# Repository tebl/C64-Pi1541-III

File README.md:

# C64 Pi1541-III
Well... if you're here, then that new and shiny SD2IEC for your Commodore 64 wasn't cycle-exact enough for you? Sure, there are great FPGA-based solutions available that can be purchased at a premium pricepoint. For the rest of us who are either on a tight budget - or - simply want something that they can build at home, then the excellent Pi1541-software written by Steve White may very well be the solution you've been looking for. With a Raspberry Pi 3 at its core, it is able to provide cycle-exact disk drive emulation with many improvements over the drive you had in your youth!

A Pi1541 can be constructed in many ways, but even though you can easily build one without the help of a PCB such as the ones provided by this project - I've found it a lot easier to make them work when you have a PCB available. I've released the design files for a more traditional Raspberry Pi-hat if you would rather build one of those, these can be found in my old repository at [C64-Pi1541-Module](https://github.com/tebl/C64-Pi1541-Module). A slightly different take on the device can also be found at [C64-Pi1541-II](https://github.com/tebl/C64-Pi1541-II) as it was made to resemble a slightly smaller stack of floppy disks.

With this third version I've instead attempted to make one that's more akin to a modern device, incorporating a 1.3" OLED on the front as being controlled via the use of a rotary encoder. While the design aesthetic makes it slightly harder to build than your standard Pi1541, I believe that it more than makes up for it.

- [1> Modules](#1-modules)
- [2> Documentation](#2-documentation)
  - [2.1> Resources](#21-resources)
- [3> Acknowledgements](#3-acknowledgements)

## 1> Modules
A complete Pi1541 requires no less than five PCBs in order to be built as pictured, for a somewhat simpler build you may skip the bottom faceplate though that also serves a purpose and it wouldn't entirely be complete without it. See below for a side view of how the device is put together, there is a top and bottom faceplate as well as another faceplate on the front. The PCB at the center will in the documentation be referred to as the *Pi1541-III Module* while the smaller one towards the front will be referred to as the *panel*.

In order to keep things in an order that's mostly organized, I've had to separate out information such as the *BOM* that goes into the build for the modules they belong to - hopefully making things easier if I ever start doing alternate versions with other components. See further below for [documentation](#2-documentation) on how to assemble one, set it up as well as anything else that you might need to know.

| Module                 | Required    | Description                        | Documentation                      | Order      |
| ---------------------- | ----------- | ---------------------------------- | ---------------------------------- | ---------- |
| [C64 Pi1541-III Module](https://github.com/tebl/C64-Pi1541-III/tree/main/C64%20Pi1541-III%20Module) | Yes | Main module |  [BOM](https://github.com/tebl/C64-Pi1541-III/tree/main/C64%20Pi1541-III%20Module/README.md#3-bom) | [PCBWay](https://www.pcbway.com/project/shareproject/C64_Pi1541_III_Module_629bebca.html)
| [C64 Pi1541-III Module Panel](https://github.com/tebl/C64-Pi1541-III/tree/main/C64%20Pi1541-III%20Module%20Panel) | Yes | Adds a vertical surface for mounting switches and rotary encoder. |  [BOM](https://github.com/tebl/C64-Pi1541-III/tree/main/C64%20Pi1541-III%20Module%20Panel/README.md#3-bom) | [PCBWay](https://www.pcbway.com/project/shareproject/C64_Pi1541_III_Panel_39049bfb.html)
| [C64 Pi1541-III Faceplate (FB1)](https://github.com/tebl/C64-Pi1541-III/tree/main/faceplates/C64%20Pi1541-III%20Module%20FB1) | Yes | Top faceplate, provides mechanical support for front panel. | | [PCBWay](https://www.pcbway.com/project/shareproject/C64_Pi1541_III_Faceplate_FB1_d125443d.html)
| [C64 Pi1541-III Faceplate (FB2)](https://github.com/tebl/C64-Pi1541-III/tree/main/faceplates/C64%20Pi1541-III%20Module%20FB2) | Recommended | Bottom faceplate, adds a layer of security so that you don't accidentally short out the device on something placed under it. | | [PCBWay](https://www.pcbway.com/project/shareproject/C64_Pi1541_III_Faceplate_FB2_912f9cbb.html)
| [C64 Pi1541-III Faceplate (FP1)](https://github.com/tebl/C64-Pi1541-III/tree/main/faceplates/C64%20Pi1541-III%20Module%20FP1) | Recommended | Front faceplate, this is mainly here to make things look nice. | | [PCBWay](https://www.pcbway.com/project/shareproject/C64_Pi1541_III_Faceplate_FP1_228805ce.html)

# 2> Documentation
There are many things that need to be said in order to successfully put a working Pi1541 together, and while the information may seem pedantic and at that times simplified for veterans at building electronical devices - I'm just an amateur and so I try to include everything that would have been needed when I first started building things such as this.

If you've just come across this page and have been wondering exactly what components you need to order in order to build the Pi1541, then I suggest that you start on the [modules](#1-modules)-section - each of modules listed are PCBs that you will most likely want. In the same list there is a link to the BOM belonging to that specific module, you need to order the components for each of them.

This repository does not include Gerber-files, you either need to generate those from the KiCAD source files found in this repository - the easiest way to order them via [PCBWay](https://www.pcbway.com/project/shareproject/?tag=Pi1541-III). Note that for the faceplates specifically, you may want to pay a little bit extra to avoid having the order number printed on it - or specifically tell them to put it on the back.

For everything else, I can only hope that one of the following documents will provide you with the answers that you need:
- [Assembling one](https://github.com/tebl/C64-Pi1541-III/blob/main/documentation/assembling_one.md)
- [Setting it up](https://github.com/tebl/C64-Pi1541-III/blob/main/documentation/setting_it_up.md)
- [Troubleshooting](https://github.com/tebl/C64-Pi1541-III/blob/main/documentation/troubleshooting.md)

## 2.1> Resources
- [Pi1541 Homepage](https://cbm-pi1541.firebaseapp.com/)
- [fat32format](http://ridgecrop.co.uk/index.htm?guiformat.htm)
- [Shared PCBWay projects for Pi1541-III](https://www.pcbway.com/project/shareproject/?tag=Pi1541-III)

# 3> Acknowledgements
Everything comes from something, in particular when it comes to most of my electronics projects. I mainly build things I would like to own, often doing a respin to fit my own particular style and preferences with most of the hardest parts of the designs already provided by people more knowledgable than I.

The Pi1541-III would not exist if it were not for the work of Steve White, creator of the [Pi1541](https://cbm-pi1541.firebaseapp.com/)-software that makes this jumble of PCBs come alive!

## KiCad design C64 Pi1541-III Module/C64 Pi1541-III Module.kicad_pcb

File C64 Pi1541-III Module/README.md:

# Pi1541-III Module
This is the main PCB and will hold most of the active components in the device, but note that it is designed to be used with [Pi1541-III Module Panel](https://github.com/tebl/C64-Pi1541-III/tree/main/C64%20Pi1541-III%20Module%20Panel) and has one listed in the [BOM](#3-bom). Note that the mentioned panel also has its own separate [BOM](https://github.com/tebl/C64-Pi1541-III/tree/main/C64%20Pi1541-III%20Module%20Panel/README.md#3-bom), so keep that in mind while ordering components.

- [1> Build instructions](#1-build-instructions)
- [2> Schematic](#2-schematic)
- [3> BOM](#3-bom)

# 1> Build instructions
Assembling this module is covered as part of the overall documentation, as linked below. Note that *BOM* is supplied per module, the one belonging to this module in particular is included as part of this document (click [here](#3-bom) to go there).

- [Assembling one](https://github.com/tebl/C64-Pi1541-III/blob/main/documentation/assembling_one.md)

# 2> Schematic
The supplied KiCad files should be sufficient as both a schematic and as a  starting point for ordering PCBs (basically you could just zip the contents of the export folder and upload that on a fabrication site), the schematic is also available in [PDF-format](https://github.com/tebl/C64-Pi1541-III/tree/main/documentation/schematic) and this is what you'll need to print and work your way through this things don't work as expected after assembly.

# 3> BOM
Most parts should be easy to get a hold of from your favourite local electronic component shop, but given that I don't have access to such shops where I live so everything was based on whatever I could get cheapest from eBay/AliExpress (free shipping, but plan on waiting 3-4 weeks for delivery). Components in parenthesis can be considered optional for features beyond the more basic functionality, but where's the fun in that? You deserve the complete package.

| Reference             | Item                                                              | Count | Order  |
| --------------------- | ----------------------------------------------------------------- | ----- | ------ |
| Module PCB            | PCB specific to this project                                      |     1 | [See modules](https://github.com/tebl/C64-Pi1541-III/blob/main/README.md#1-modules)
| Faceplate (FB1) PCB   | Top faceplate                                                     |     1 | [See modules](https://github.com/tebl/C64-Pi1541-III/blob/main/README.md#1-modules)
| Faceplate (FB2) PCB   | Bottom faceplate                                                  |    (1)| [See modules](https://github.com/tebl/C64-Pi1541-III/blob/main/README.md#1-modules)
| A1                    | 2x20 pin female header                                            |     1 |
|                       | Raspberry Pi version 3B,3B+ or 3A+                                |     1 |
| A2 *1                 | 4ch I2C level converter module                                    |     1 |
| BZ1                   | Passive buzzer (pin spacing from 3.81 to 7mm will work)           |   (1) |
| C1                    | 100nF ceramic capacitor (5mm)                                     |     1 |
| C6                    | 470uF electrolytic capacitor (8mm x 3.5mm)                        |     1 |
| J1                    | 2.1mm x 5.5mm barrel plug                                         |     1 |
| J2,J3                 | Female S-terminal 6-pin DIN PCB                                   |  1 (1)|
| J8                    | [Pi1541-III Module Panel](https://github.com/tebl/C64-Pi1541-III/tree/main/C64%20Pi1541-III%20Module%20Panel) (completed unit) | 1 |
| R1,R2                 | 1k Ohm resistor                                                   |     2 |
| R3,R4                 | 10k Ohm resistor                                                  |     2 |
| R6,R7 *2              | 470 Ohm resistor                                                  |     2 |
| U1 *3                 | 7406 (DIP-14)                                                     |     1 |
| Mounting *4           | Nylon M3 hex standoffs 6mm (M-F)                                  |     4 |
| Mounting *4           | Nylon M3 hex standoffs 8mm (M-F)                                  |     2 |
| Mounting *5           | Nylon M3 hex standoffs 12mm (M-F)                                 |    (4)|
| Mounting *4           | Nylon M3 hex standoffs 20mm (M-F)                                 |     4 |
| Mounting *4           | Nylon M3x6mm nylon screws                                         |     6 |
| Mounting *4           | Nylon M3x6mm nylon nuts                                           |     12 |

1) There are multiple configurations of these being sold, this is usually sold with a blue PCB. When in doubt, compare the sale listing with the one shown in this [image](https://raw.githubusercontent.com/tebl/C64-Pi1541-III/main/gallery/build_006B.jpg).
2) This is the resistor for the LEDs mounted on [Pi1541-III Module Panel](https://github.com/tebl/C64-Pi1541-III/tree/main/C64%20Pi1541-III%20Module%20Panel), the value need to be sized according to the type of LED being used. This value is a somewhat safe choice cheaper coloured LEDs, for anything blue or especially marked as being *bright* - then you need to calculate a proper value for these.
3) There are unfortunately counterfeit 7406-chips being circulated, the ones I've had the most success with has been marked 7406PC though a handful of SN7406 have also been found working. See [troubleshooting](https://github.com/tebl/C64-Pi1541-III/blob/main/documentation/troubleshooting.md) for more information.
4) These are used in various places of the project, these are available in the form of kits usually advertised *M3 nylon standoff kit* which should contain most of what you'd need though you should check that they include them in sufficient quantity.
5) These are only needed when *NOT* installing bottom faceplate ([Pi1541-III Faceplate (FB2)](https://github.com/tebl/C64-Pi1541-III/tree/main/faceplates/C64%20Pi1541-III%20Module%20FB2))

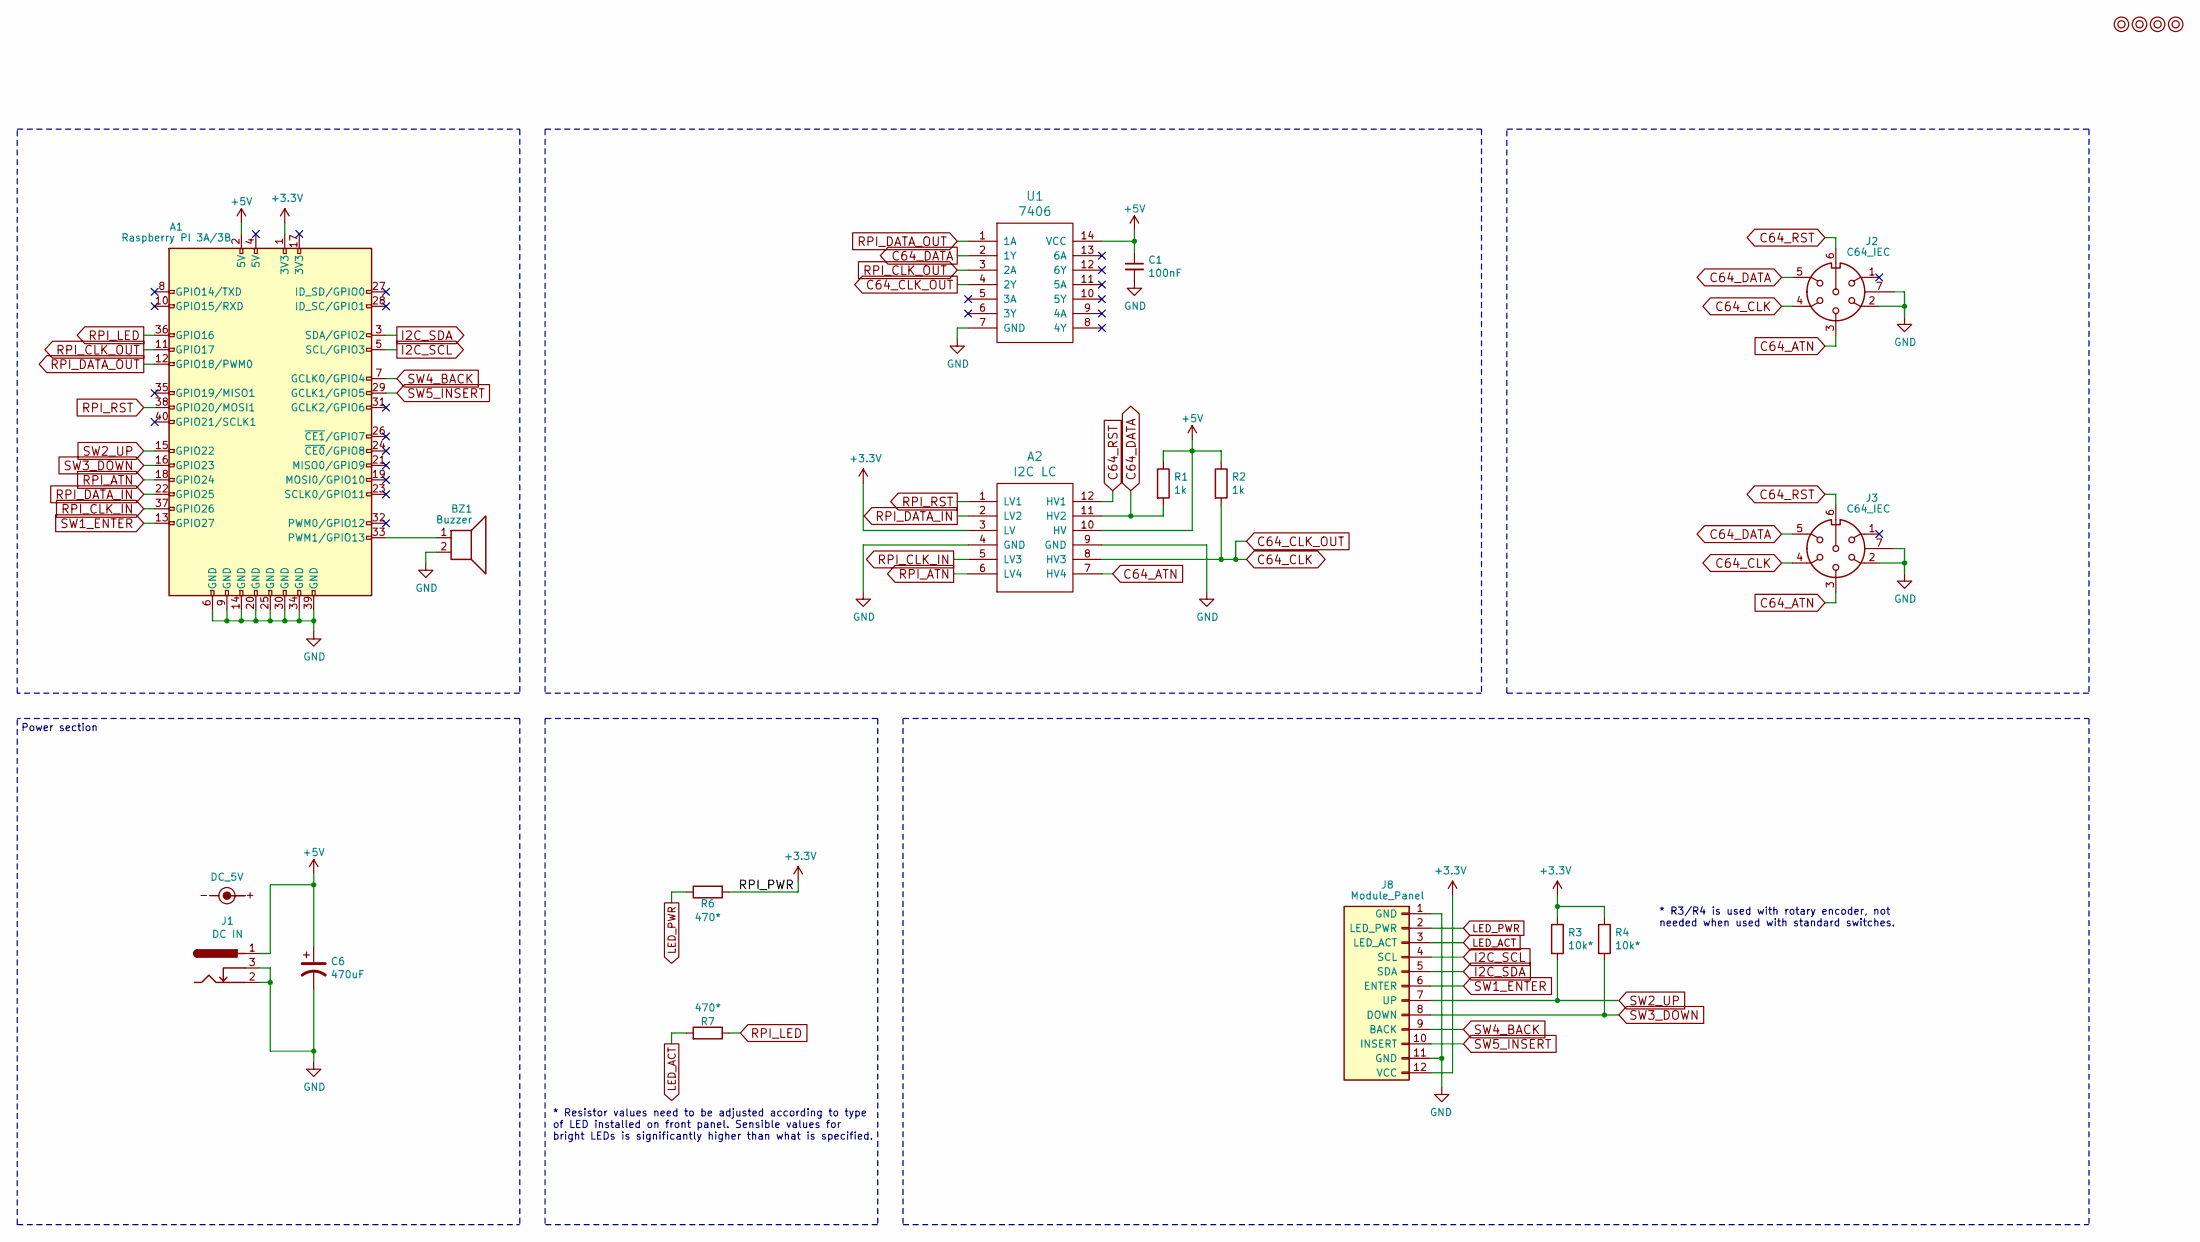
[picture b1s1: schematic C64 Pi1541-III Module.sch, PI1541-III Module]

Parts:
A1: Raspberry PI 3A/3B; Raspberry_Pi_3B_Socketed_THT_FaceDown_MountingHoles
A2: I2C LC; 4CH_I2C_Level_Converter
BZ1: Buzzer; Buzzer_12x9.5RM7.6
C1: 100nF; C_Disc_D4.7mm_W2.5mm_P5.00mm
C6: 470uF; CP_Radial_D8.0mm_P3.50mm
J1: DC IN; BARREL_JACK
J2, J3: C64_IEC; DIN6_IEC
J8: Module_Panel
M1, M2, M3, M4: Mounting; M3
R1, R2: 1k; R_Axial_DIN0207_L6.3mm_D2.5mm_P10.16mm_Horizontal
R3, R4: 10k*; R_Axial_DIN0207_L6.3mm_D2.5mm_P10.16mm_Horizontal
R6, R7: 470*; R_Axial_DIN0207_L6.3mm_D2.5mm_P10.16mm_Horizontal
SYM1: DC_5V; PWR_Specification
U1: 7406; DIP-14_W7.62mm_Socket_LongPads

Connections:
+3V3: A1.1 (3V3), A2.3 (LV), J8.12 (VCC), R3.1, R4.1, R6.2
+5V: A1.2 (5V), A2.10 (HV), C1.1, C6.1, J1.1, R1.1, R2.1, U1.14 (VCC)
C64_ATN: A2.7 (HV4), J2.3, J3.3
C64_CLK: A2.8 (HV3), J2.4, J3.4, R2.2, U1.4 (2Y)
C64_DATA: A2.11 (HV2), J2.5, J3.5, R1.2, U1.2 (1Y)
C64_RST: A2.12 (HV1), J2.6, J3.6
GND: A1.6 (GND), A1.9 (GND), A1.14 (GND), A1.20 (GND), A1.25 (GND), A1.30 (GND), A1.34 (GND), A1.39 (GND), A2.4 (GND), A2.9 (GND), BZ1.2, C1.2, C6.2, J1.2, J1.3, J2.2, J2.7, J3.2, J3.7, J8.1 (GND), J8.11 (GND), U1.7 (GND)
I2C_SCL: A1.5 (SCL/GPIO3), J8.4 (SCL)
I2C_SDA: A1.3 (SDA/GPIO2), J8.5 (SDA)
LED_ACT: J8.3 (LED_ACT), R7.2
LED_PWR: J8.2 (LED_PWR), R6.1
unnamed: A1.33 (PWM1/GPIO13), BZ1.1
RPI_ATN: A1.18 (GPIO24), A2.6 (LV4)
RPI_CLK_IN: A1.37 (GPIO26), A2.5 (LV3)
RPI_CLK_OUT: A1.11 (GPIO17), U1.3 (2A)
RPI_DATA_IN: A1.22 (GPIO25), A2.2 (LV2)
RPI_DATA_OUT: A1.12 (GPIO18/PWM0), U1.1 (1A)
RPI_LED: A1.36 (GPIO16), R7.1
RPI_RST: A1.38 (GPIO20/MOSI1), A2.1 (LV1)
SW1_ENTER: A1.13 (GPIO27), J8.6 (ENTER)
SW2_UP: A1.15 (GPIO22), J8.7 (UP), R3.2
SW3_DOWN: A1.16 (GPIO23), J8.8 (DOWN), R4.2
SW4_BACK: A1.7 (GCLK0/GPIO4), J8.9 (BACK)
SW5_INSERT: A1.29 (GCLK1/GPIO5), J8.10 (INSERT)

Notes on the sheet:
Power section
* R3/R4 is used with rotary encoder, not needed when used with standard switches.
* Resistor values need to be adjusted according to type of LED installed on front panel. Sensible values for bright LEDs is significantly higher than what is specified.

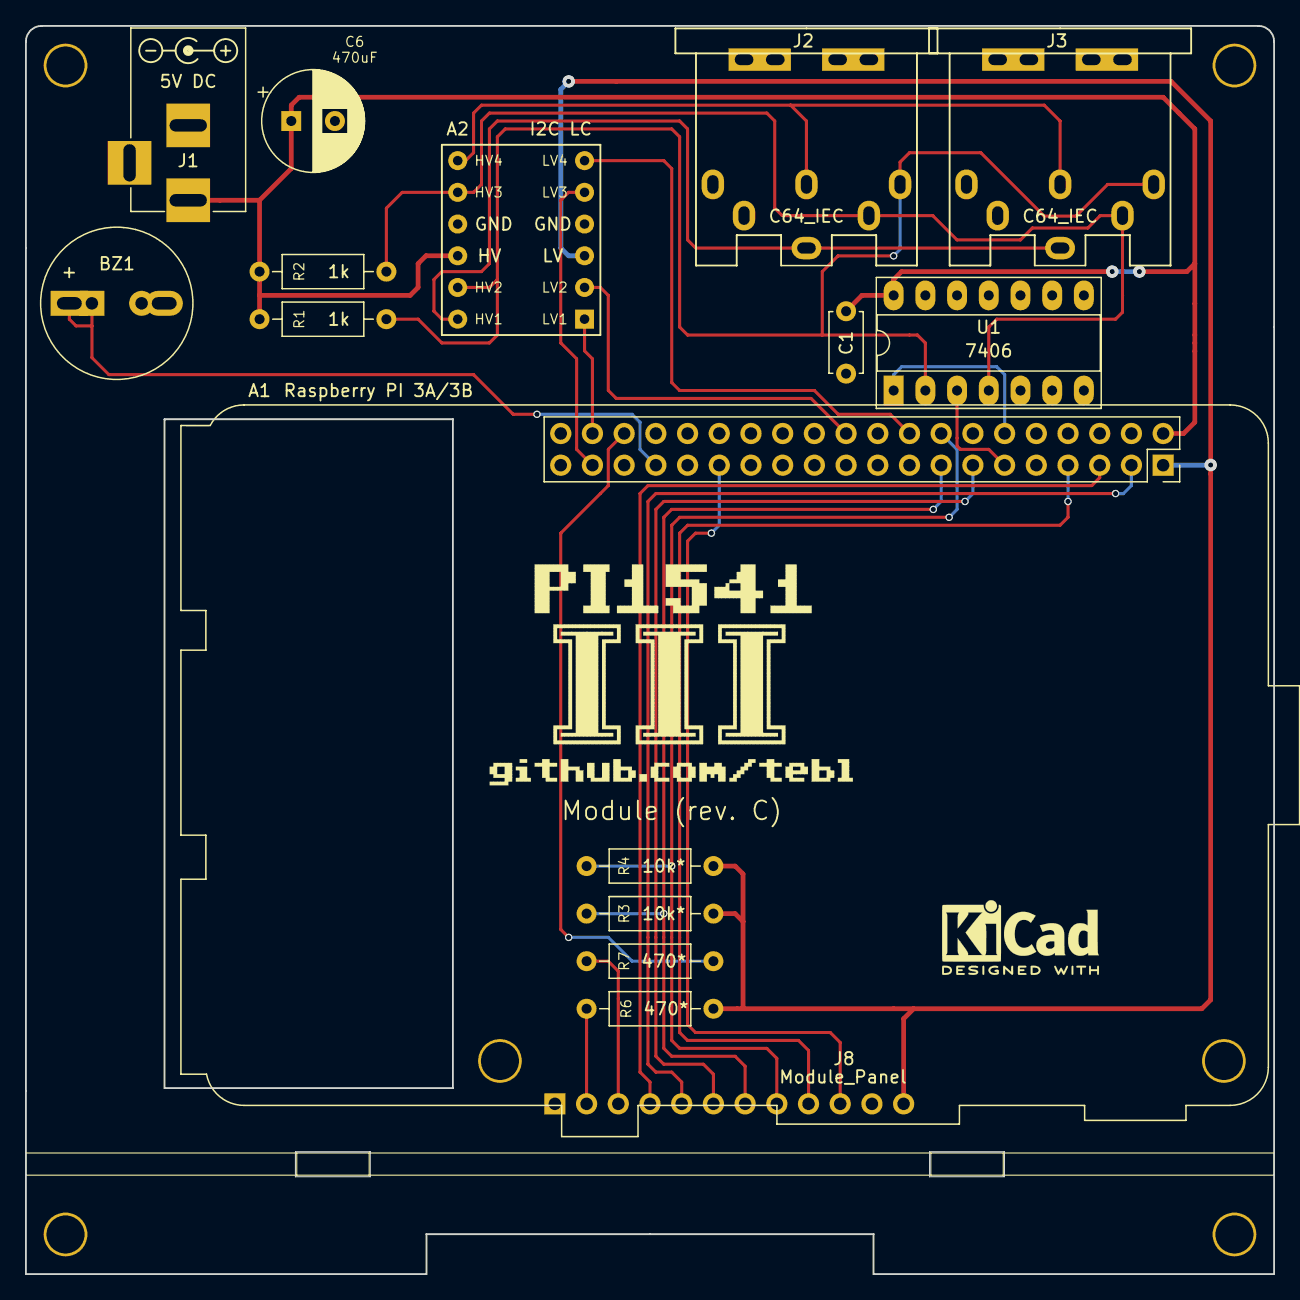
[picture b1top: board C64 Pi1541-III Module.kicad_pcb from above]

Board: 2 copper layers, 100.0 x 100.0 mm, 22 parts (1 on the bottom side), 24 nets.

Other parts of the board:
Pi1541-drive: Pi1541-drive

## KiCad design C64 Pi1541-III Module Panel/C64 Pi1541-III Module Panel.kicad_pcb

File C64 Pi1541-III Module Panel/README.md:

# Pi1541-III Module Panel
This PCB holds the components for the front panel, it was designed to mount on top of [Pi1541-III Module](https://github.com/tebl/C64-Pi1541-III/tree/main/C64%20Pi1541-III%20Module). This panel has its own BOM, so keep that in mind when ordering components - as you'll be needing parts listed for both of them to build a complete device.

- [1> Build instructions](#1-build-instructions)
- [2> Schematic](#2-schematic)
- [3> BOM](#3-bom)

# 1> Build instructions
Assembling this module is covered as part of the overall documentation, as linked below. Note that *BOM* is supplied per module, the one belonging to this module in particular is included as part of this document (click [here](#3-bom) to go there).
- [Assembling one](https://github.com/tebl/C64-Pi1541-III/blob/main/documentation/assembling_one.md)

# 2> Schematic
The supplied KiCad files should be sufficient as both a schematic and as a  starting point for ordering PCBs (basically you could just zip the contents of the export folder and upload that on a fabrication site), the schematic is also available in [PDF-format](https://github.com/tebl/C64-Pi1541-III/tree/main/documentation/schematic) and this is what you'll need to print and work your way through this things don't work as expected after assembly.

# 3> BOM
Most parts should be easy to get a hold of from your favourite local electronic component shop, but given that I don't have access to such shops where I live so everything was based on whatever I could get cheapest from eBay/AliExpress (free shipping, but plan on waiting 3-4 weeks for delivery). Components in parenthesis can be considered optional for features beyond the more basic functionality, but where's the fun in that? You deserve the complete package.

| Reference             | Item                                                              | Count | Order  |
| --------------------- | ----------------------------------------------------------------- | ----- | ------ |
| Module Panel PCB      | PCB specific to this project                                      |     1 | [See modules](https://github.com/tebl/C64-Pi1541-III/blob/main/README.md#1-modules)
| Faceplate (FP1) PCB   | Front faceplate                                                   |    (1)| [See modules](https://github.com/tebl/C64-Pi1541-III/blob/main/README.md#1-modules)
| IC1 *1                | SH1106 I2C OLED 128x64 (1.3")                                     |     1 |
| ENC1                  | EC11 rotary encoder, 20mm. Preferably plum handle.                |     1 |
|                       | Suitable knob for rotary encoder, max 20mm in diameter.           |    (1)|
| D1,D2                 | 2x5x7mm rectangular LED, suitably coloured.                       |     2 |
| J1                    | 12-pin right-angle pin header                                     |     1 |
| SW1,SW2               | 6x6mm momentary switch, 10.5mm or taller.                         |     2 |
| Mounting *2           | Nylon M3 hex standoffs 8mm (M-F)                                  |     4 |
| Mounting *2           | Nylon M3x6mm nylon screws                                         |     4 |
| Mounting *2           | Nylon M3x6mm nylon nuts                                           |     4 |

1) Many of these will be listed for sale as 1.3" ssd1306-based OLED displays, but they actually have the slightly different sh1106-controller. Something to keep in mind when ordering.
2) These are used in various places of the project, these are available in the form of kits usually advertised *M3 nylon standoff kit* which should contain most of what you'd need though you should check that they include them in sufficient quantity.

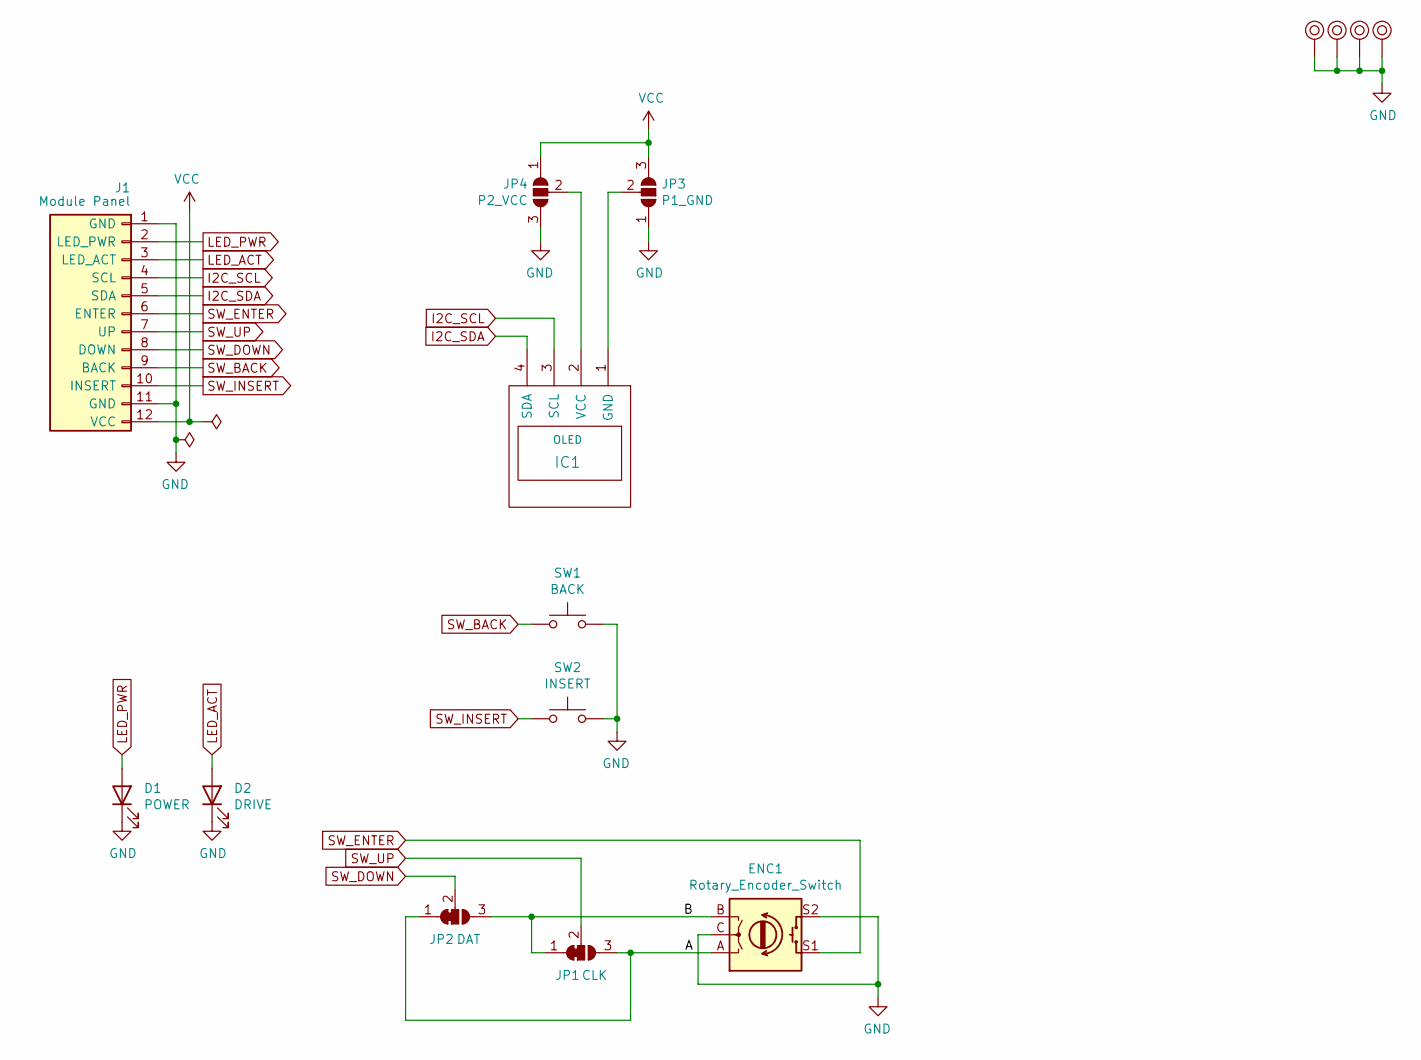
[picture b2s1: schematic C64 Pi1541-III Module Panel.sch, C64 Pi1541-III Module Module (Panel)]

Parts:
D1: POWER; LED_Rectangular_W3.0mm_H2.0mm
D2: DRIVE; LED_Rectangular_W3.0mm_H2.0mm
ENC1: Rotary_Encoder_Switch; RotaryEncoder_Alps_EC11E-Switch_Vertical_H20mm
IC1: OLED; 1.3_I2C_OLED_No_mounting
J1: Module Panel; PinHeader_1x12_P2.54mm_Horizontal
JP1: CLK; SolderJumper-3_P1.3mm_Open_Pad1.0x1.5mm
JP2: DAT; SolderJumper-3_P1.3mm_Open_Pad1.0x1.5mm
JP3: P1_GND; SolderJumper-3_P1.3mm_Open_Pad1.0x1.5mm
JP4: P2_VCC; SolderJumper-3_P1.3mm_Open_Pad1.0x1.5mm
M1, M2, M3, M4: Mounting_Pin; M3_pin
SW1: BACK; SW_PUSH_6mm
SW2: INSERT; SW_PUSH_6mm

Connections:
/A: ENC1.A, JP1.3 (B), JP2.1 (A)
/B: ENC1.B, JP1.1 (A), JP2.3 (B)
GND: D1.1 (K), D2.1 (K), ENC1.C, ENC1.S2, J1.1 (GND), J1.11 (GND), JP3.1 (A), JP4.3 (B), M1.1, M2.1, M3.1, M4.1, SW1.2, SW2.2
I2C_SCL: IC1.3 (SCL), J1.4 (SCL)
I2C_SDA: IC1.4 (SDA), J1.5 (SDA)
LED_ACT: D2.2 (A), J1.3 (LED_ACT)
LED_PWR: D1.2 (A), J1.2 (LED_PWR)
unnamed: IC1.1 (GND), JP3.2 (C)
unnamed: IC1.2 (VCC), JP4.2 (C)
SW_BACK: J1.9 (BACK), SW1.1
SW_DOWN: J1.8 (DOWN), JP2.2 (C)
SW_ENTER: ENC1.S1, J1.6 (ENTER)
SW_INSERT: J1.10 (INSERT), SW2.1
SW_UP: J1.7 (UP), JP1.2 (C)
VCC: J1.12 (VCC), JP3.3 (B), JP4.1 (A)

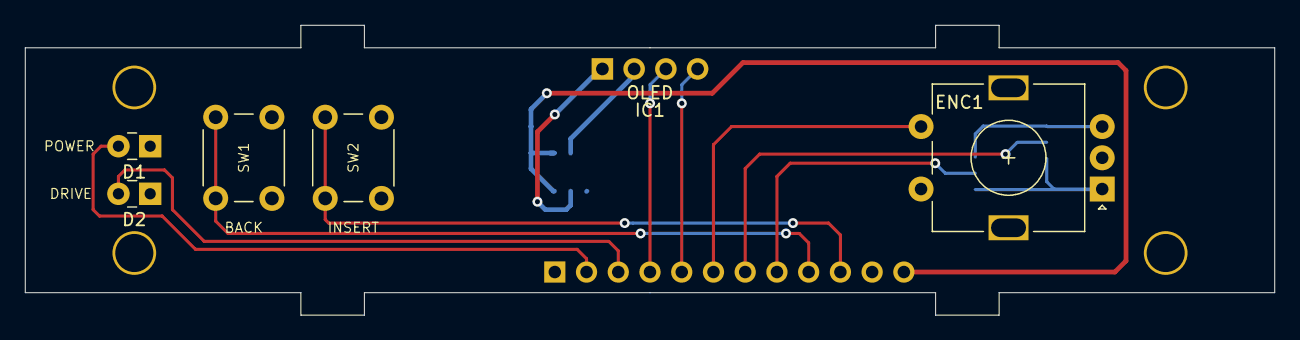
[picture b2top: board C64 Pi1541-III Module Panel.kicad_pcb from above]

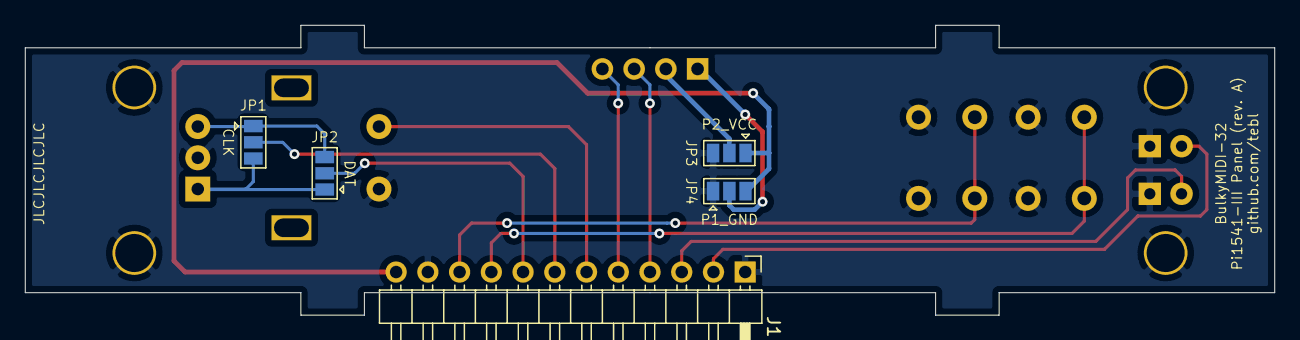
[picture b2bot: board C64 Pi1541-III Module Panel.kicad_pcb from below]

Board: 2 copper layers, 100.0 x 23.2 mm, 15 parts (5 on the bottom side), 15 nets.

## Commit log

2023-03-08 Main module added
2023-03-09 First layout done
2023-03-23 Fix DIN-footprint
2023-03-23 Adjust cutout for LEDs slightly
2023-03-23 Tweak footprint placement
2023-03-23 Lock footprint
2023-03-23 Changed decal wording
2023-03-23 Added bottom plate design
2023-03-23 Adjust LED resistor value
2023-03-26 Script for converting XBM-files for use with LcdLogoName (custom boot logo)
2023-03-26 Exported files
2023-04-04 Moved components around to make it easier to build
2023-09-01 License
2023-09-01 Add images
2023-09-02 Add BOMs
2023-09-02 Swap pictures
2023-09-02 Documentation placeholder
2023-09-30 Add image
2024-06-06 Ko-fi
